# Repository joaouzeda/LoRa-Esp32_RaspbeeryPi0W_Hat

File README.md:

<h1 align="center"> LoRa-Esp32 Hat to a Raspberry Pi Zero W  </h1>

<h2 align="center"> Project Description </h2>
An Esp32 with LoRa to connect with a Raspberry Pi Zero W using serial Pins.

<br/>

<h2 align="center"> General Information </h2>

Board: Raspberry Pi Zero W<br/>
Microcontrooler: Esp32 Wroom 32D<br/>
LoRa: Wio Sx1262<br/>
Date: 2026, April <br/>

<h2 align="center"> Autores </h2>

[<br></sub>João Uzêda</sub>](https://github.com/joaouzeda) 

# *Badges*

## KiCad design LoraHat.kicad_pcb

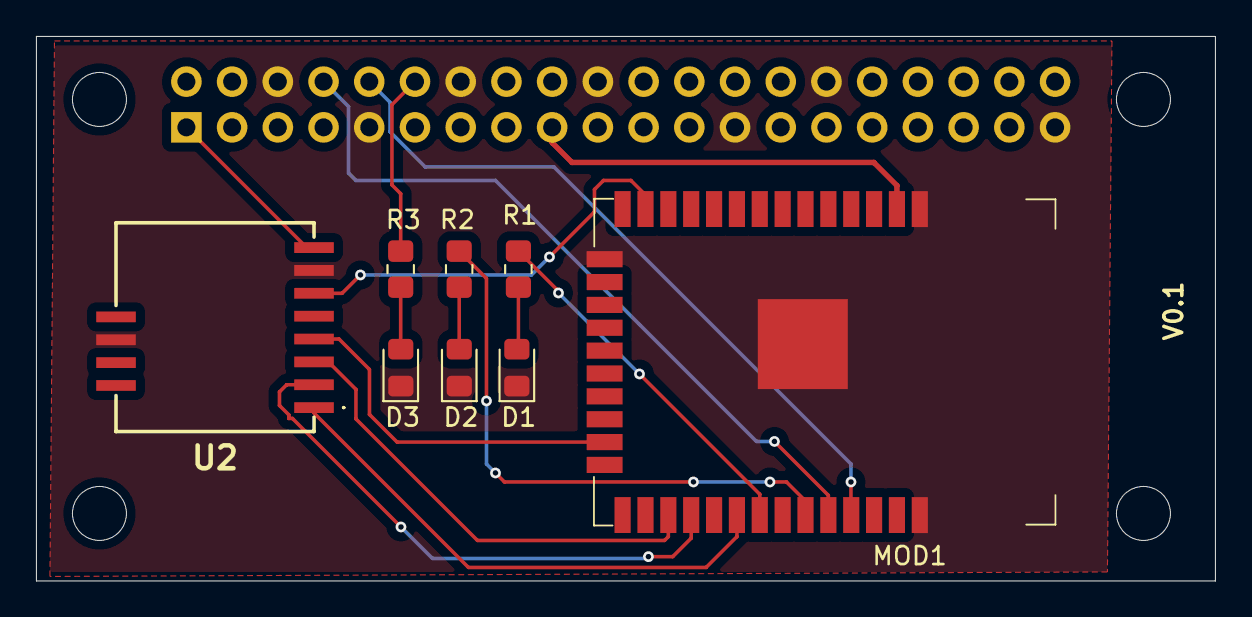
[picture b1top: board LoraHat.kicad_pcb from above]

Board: 2 copper layers, 65.5 x 30.2 mm, 9 parts (1 on the bottom side), 15 nets.

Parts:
D1, D2, D3: LED; LED_0805_2012Metric_Pad1.15x1.40mm_HandSolder
J1-Raspberry1: Conn_02x20_Odd_Even; PinSocket_2x20_P2.54mm_Vertical
MOD1: ESP32-WROOM-32; ESP32-WROOM-32D
R1: 330 Ohms; R_0805_2012Metric_Pad1.20x1.40mm_HandSolder
R2, R3: 330 Ohmns; R_0805_2012Metric_Pad1.20x1.40mm_HandSolder
U2: Wio-SX1262; WioSX1262

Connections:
+3.3V: J1-Raspberry1.1, J1-Raspberry1.17, MOD1.2 (3V3), U2.8 (VCC)
/Serial_1: J1-Raspberry1.10, MOD1.35 (TXD0)
/Serial_2: J1-Raspberry1.8, MOD1.34 (RXD0)
GND: D1.1 (K), D2.1 (K), D3.1 (K), J1-Raspberry1.6, J1-Raspberry1.9, J1-Raspberry1.14, J1-Raspberry1.20, J1-Raspberry1.25, J1-Raspberry1.30, J1-Raspberry1.39, MOD1.1 (GND), MOD1.15 (GND), MOD1.38 (GND), MOD1.39 (GND), U2.7 (GND1), U2.10 (GND2)
unnamed: D1.2 (A), R1.2
unnamed: D2.2 (A), R2.2
unnamed: D3.2 (A), R3.2
unnamed: J1-Raspberry1.12, R3.1
unnamed: MOD1.13 (IO14), U2.6 (NSS)
unnamed: MOD1.23 (IO15), U2.4 (SCK)
unnamed: MOD1.27 (IO16), U2.3 (MOSI)
unnamed: MOD1.28 (IO17), U2.2 (MISO)
unnamed: MOD1.30 (IO18), U2.1 (RF_SW1)
unnamed: MOD1.31 (IO19), R1.1
unnamed: MOD1.33 (IO21), R2.1

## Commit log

2026-04-19 V0.1
